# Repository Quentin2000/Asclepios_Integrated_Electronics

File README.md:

# Master Project

## Integration of a miniaturized O2 sensor into a space suit helmet.

#### Author: Quentin Delfosse
#### Academic Supervisor: Pr. Guillermo Villanueva
#### Technical Supervisor: Arnault Monoyer

## Repository files

This repository includes the following design files:
- **HW**: Kicad hardware files for the interface board and air quality sensor board.
- **SW**: Arduino files used to flash the ESP32 S2 Mini 1 computer.
- **SD**: Setup files for the SD card.

To access CAD design files, please refer to the Google Drive: https://drive.google.com/drive/folders/1vZVMf6BT2zpStATiHxgfttCtssU6DIhK?usp=drive_link.

## Introduction

Asclepios is a student-led project from Switzerland aiming at organizing simulations of manned space missions. For this purpose, the association rents existing infrastructure and builds its base inside. Therefore, by design, the mission will take place on Earth, where many parameters are different than on other celestial bodies. However, the analog astronauts will live together in close contact during the two weeks of the mission to experience the constraints of extraterrestrial environments during the Earth-based simulation. The project aims at optimizing their environment to make their mission as realistic as possible.

<br />

This project aims at integrating a miniaturized O2 sensor into a space suit helmet to monitor the user's breathable atmosphere. Both mechanical and electrical sensor integration will be required. Additionally, the sensor data will need to be processed. Thus, a graphical interface for the visualization of the O2 data in real time will need to be created.

<p align="center">
</img>
</p>

## Setup

### Hardware

The system is made of 3 stacked layers:
- **Upper stage**: Sensor stage (O2 + Air quality sensors)
- **Middle stage**: Interface stage 
- **Lower stage**: Main computer stage (ESP32 S2 Mini 1)

**CAREFUL: Before connecting two boards together, please make sure that the signals on both end match! This can be checked on the surface of the boards! Otherwise you may fry the sensors and the computer!**

To assemble the system, simply stack the layers on top of each other:
- Connect the main computer board (black one) to the interface board (long green one).
- **Make sure to check that the signals match: 3V3, Ground, 5V!**
- Insert the SD card into the interface board (bottom face).
- Connect the screen to the interface board (long white connector).
- Connect the Air quality sensor board (small green one) on top of the rooting board (long green one).
- **Again, check that the signals match: 3V3, Ground, 5V!**
- Place the stacked-up module on the 4 rails of the bottom cover. Only one orientation should fit.
- Connect the O2 sensor cable to the O2 sensor board.
- Insert the O2 sensor into the top cover hole, following the 2 rails and making sure that its cable comes out through the dedicated hole on the side.
- Place a foam on top of the interface board where the O2 sensor will be positioned (next to the air quality sensor).
- Close both end on the case together.
- Plug a USB cable to the micro usb port of the main computer and connect it to the portable battery.
- Power up the battery.

The screen should initialize after a couple of seconds and show a similar screen as the following one:
<p align="center">
</img>
</p>

The following figure shows a guidethrough of the procedure.
<p align="center">
</img>
</p>

### Software

To display the sensors data, you will need the following package:
```ruby
pip install pandas 
```

To retrieve the data from the SD card, the following procedure must be applied:
- Plug it into your computer
- Open the SD card folder and check the mission log which you want to display
- Open a terminal window
- Go to the SD card directory, something like the following for MAC OS users.
```ruby
 cd /Volumes/NO\ NAME 
```
- Type the following command, where **x** is the number of the mission log to display. You may also need to change to **python** instead of **python3** depending on your computer
```ruby
python3 display.py mission_log_x 
```

This will create a png file with the sensor graphs over the mission duration and an excel file with these values.
<p align="center">
</img>
</p>

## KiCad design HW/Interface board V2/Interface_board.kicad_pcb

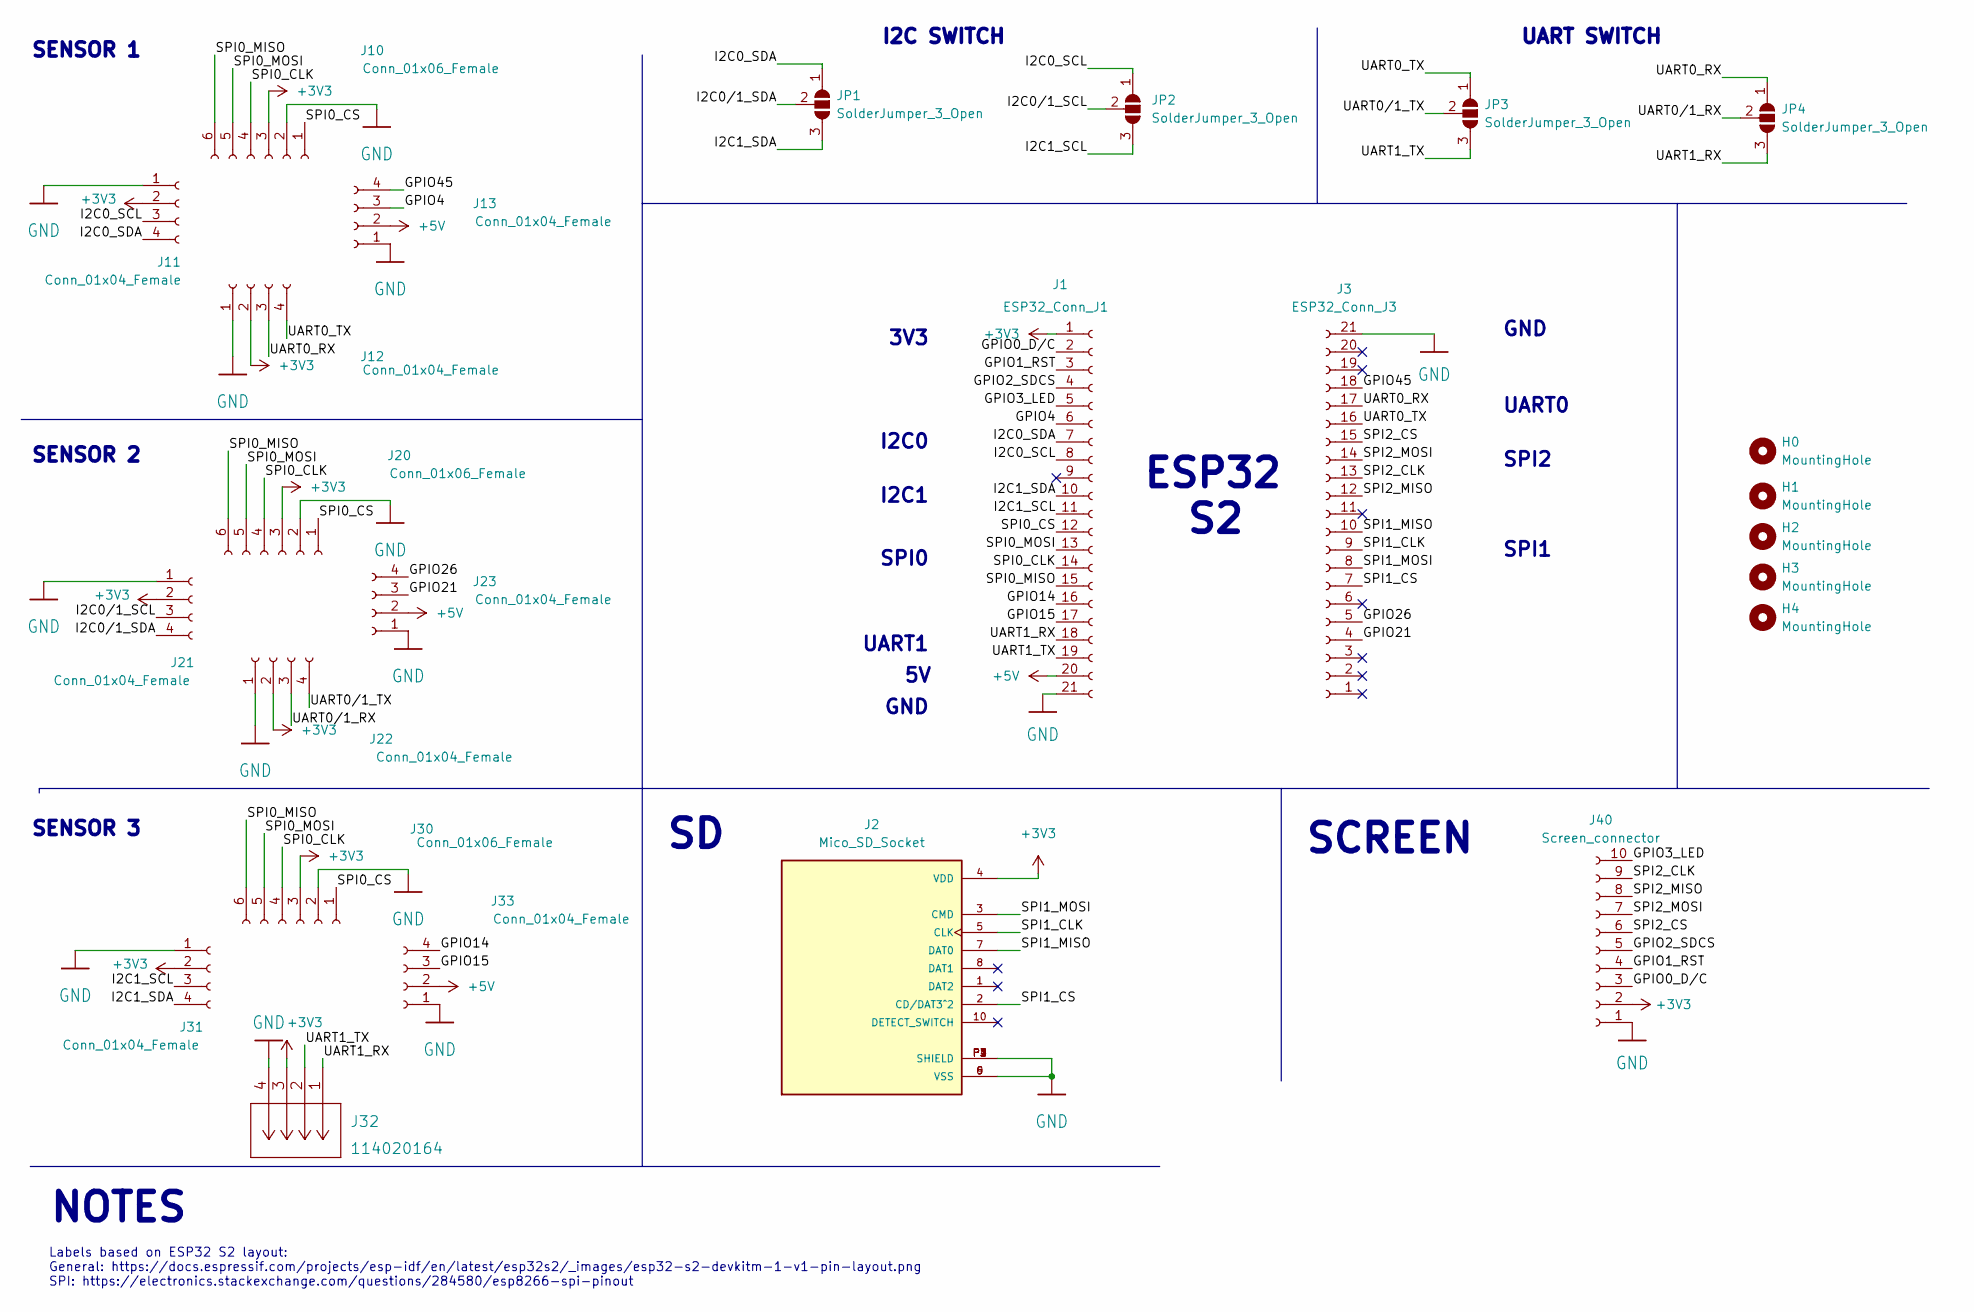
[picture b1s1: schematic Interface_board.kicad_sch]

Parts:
H0, H1, H2, H3, H4: MountingHole; MountingHole_2.2mm_M2_DIN965_Pad_TopBottom
J1: ESP32_Conn_J1; PinHeader_1x21_P2.54mm_Vertical
J2: Mico_SD_Socket; MOLEX_503398-1892; PARTREV 0
J3: ESP32_Conn_J3; PinHeader_1x21_P2.54mm_Vertical
J10, J20, J30: Conn_01x06_Female; PinSocket_1x06_P2.54mm_Vertical
J11, J12, J13, J21, J22, J23, J31, J33: Conn_01x04_Female; PinSocket_1x04_P2.54mm_Vertical
J32: 114020164; Conn_seed_114020164
J40: Screen_connector; Molex_PicoBlade_53048-1010_1x10_P1.25mm_Horizontal
JP1, JP2, JP3, JP4: SolderJumper_3_Open; SolderJumper-3_P1.3mm_Open_RoundedPad1.0x1.5mm

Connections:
+3V3: J1.1, J2.4 (VDD), J10.3, J11.2, J12.2, J20.3, J21.2, J22.2, J30.3, J31.2, J32.3, J40.2
+5V: J1.20, J13.2, J23.2, J33.2
/GPIO0_D/C: J1.2, J40.3
/GPIO1_RST: J1.3, J40.4
/GPIO2_SDCS: J1.4, J40.5
/GPIO3_LED: J1.5, J40.10
/GPIO4: J1.6, J13.3
/GPIO14: J1.16, J33.4
/GPIO15: J1.17, J33.3
/GPIO21: J3.4, J23.3
/GPIO26: J3.5, J23.4
/GPIO45: J3.18, J13.4
/I2C0_SCL: J1.8, J11.3, JP2.1 (A)
/I2C0_SDA: J1.7, J11.4, JP1.1 (A)
/I2C0/1_SCL: J21.3, JP2.2 (C)
/I2C0/1_SDA: J21.4, JP1.2 (C)
/I2C1_SCL: J1.11, J31.3, JP2.3 (B)
/I2C1_SDA: J1.10, J31.4, JP1.3 (B)
/SPI0_CLK: J1.14, J10.4, J20.4, J30.4
/SPI0_CS: J1.12, J10.1, J20.1, J30.1
/SPI0_MISO: J1.15, J10.6, J20.6, J30.6
/SPI0_MOSI: J1.13, J10.5, J20.5, J30.5
/SPI1_CLK: J2.5 (CLK), J3.9
/SPI1_CS: J2.2 (CD/DAT3^2), J3.7
/SPI1_MISO: J2.7 (DAT0), J3.10
/SPI1_MOSI: J2.3 (CMD), J3.8
/SPI2_CLK: J3.13, J40.9
/SPI2_CS: J3.15, J40.6
/SPI2_MISO: J3.12, J40.8
/SPI2_MOSI: J3.14, J40.7
/UART0_RX: J3.17, J12.3, JP4.1 (A)
/UART0_TX: J3.16, J12.4, JP3.1 (A)
/UART0/1_RX: J22.3, JP4.2 (C)
/UART0/1_TX: J22.4, JP3.2 (C)
/UART1_RX: J1.18, J32.1, JP4.3 (B)
/UART1_TX: J1.19, J32.2, JP3.3 (B)
GND: J1.21, J2.6 (VSS), J2.9 (VSS), J2.P1 (SHIELD), J2.P2 (SHIELD), J2.P3 (SHIELD), J2.P4 (SHIELD), J3.21, J10.2, J11.1, J12.1, J13.1, J20.2, J21.1, J22.1, J23.1, J30.2, J31.1, J32.4, J33.1, J40.1

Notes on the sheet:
SENSOR 3
SCREEN
GND
UART1
Labels based on ESP32 S2 layout: General: https://docs.espressif.com/projects/esp-idf/en/latest/esp32s2/_images/esp32-s2-devkitm-1-v1-pin-layout.png SPI: https://electronics.stackexchange.com/questions/284580/esp8266-spi-pinout
3V3
I2C SWITCH
I2C1
ESP32 S2
I2C0
SPI1
SPI0
SENSOR 1
NOTES
UART0
UART SWITCH
SPI2
SENSOR 2

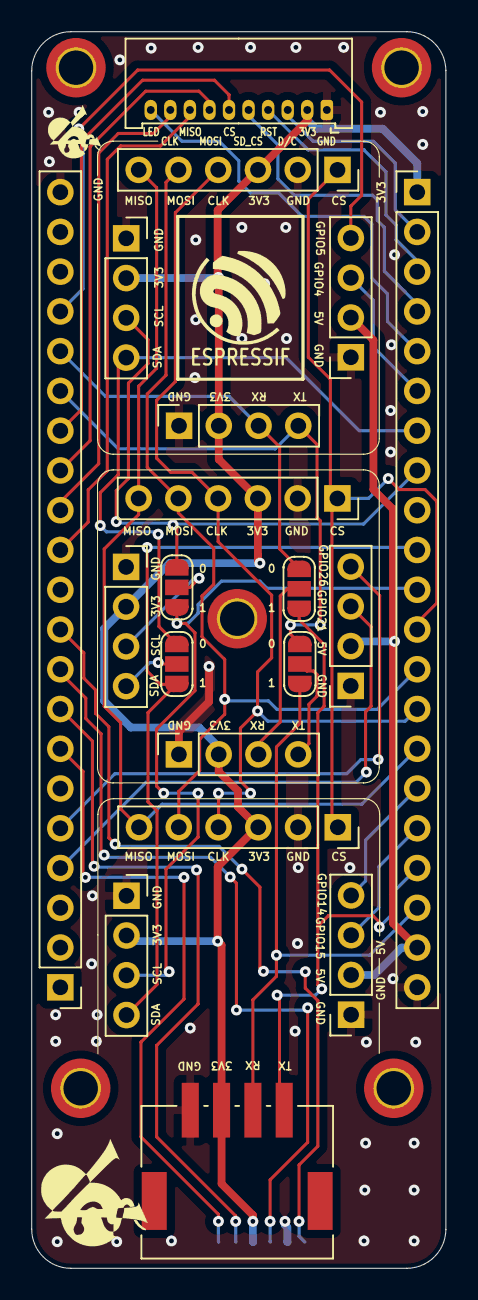
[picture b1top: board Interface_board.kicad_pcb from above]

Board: 2 copper layers, 26.5 x 79.0 mm, 25 parts (1 on the bottom side), 37 nets.

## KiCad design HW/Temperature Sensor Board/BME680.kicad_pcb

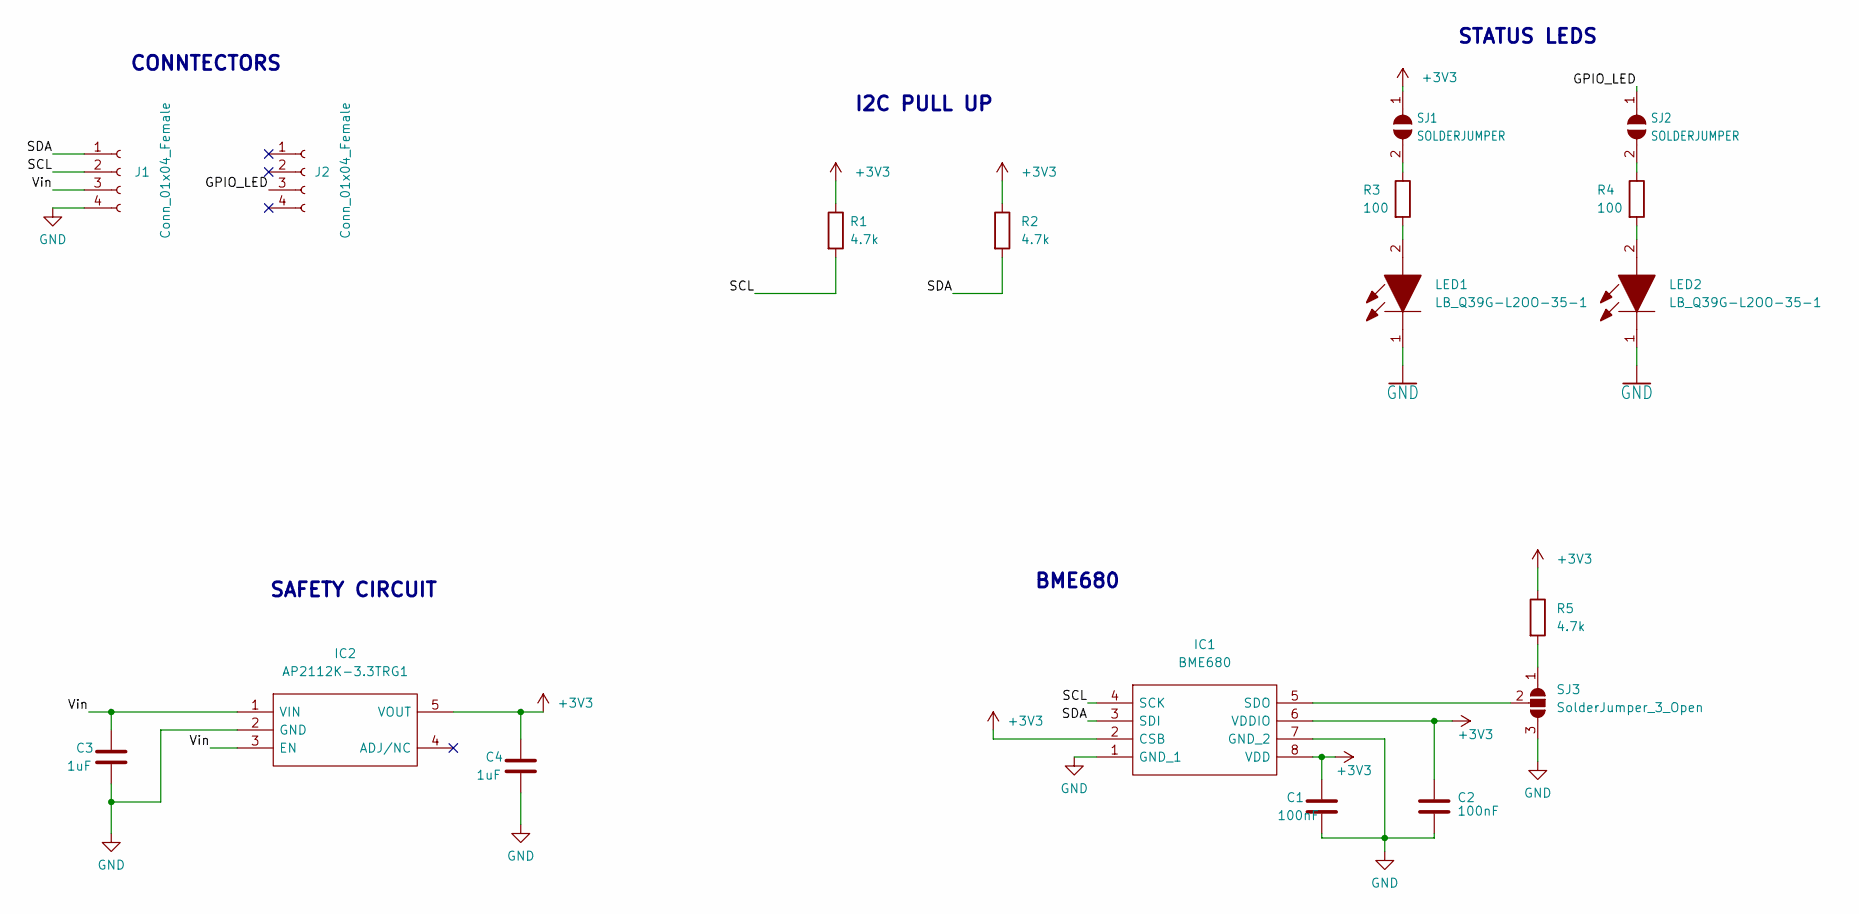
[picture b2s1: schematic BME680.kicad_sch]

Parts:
C1, C2: 100nF; C_0603_1608Metric
C3, C4: 1uF; C_0603_1608Metric
IC1: BME680; Mouser Part Number 262-BME680
IC2: AP2112K-3.3TRG1; SOT95P282X130-5N; Mouser Part Number 621-AP2112K-3.3TRG1
J1, J2: Conn_01x04_Female; PinHeader_1x04_P2.54mm_Vertical
LED1, LED2: LB_Q39G-L2OO-35-1; LEDC1608X40N; Mouser Part Number 720-LBQ39GL2N2351
R1, R2, R5: 4.7k; R_0603_1608Metric
R3, R4: 100; R_0603_1608Metric
SJ1, SJ2: SOLDERJUMPER; SolderJumper-2_P1.3mm_Open_RoundedPad1.0x1.5mm
SJ3: SolderJumper_3_Open; SolderJumper-3_P1.3mm_Open_RoundedPad1.0x1.5mm

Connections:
+3V3: C1.1, C2.1, C4.1, IC1.2 (CSB), IC1.6 (VDDIO), IC1.8 (VDD), IC2.5 (VOUT), R1.1, R2.1, R5.1, SJ1.1
/GPIO_LED: J2.3, SJ2.1
/SCL: IC1.4 (SCK), J1.2, R1.2
/SDA: IC1.3 (SDI), J1.1, R2.2
/Vin: C3.1, IC2.1 (VIN), IC2.3 (EN), J1.3
GND: C1.2, C2.2, C3.2, C4.2, IC1.1 (GND_1), IC1.7 (GND_2), IC2.2 (GND), J1.4, LED1.1, LED2.1, SJ3.3 (B)
unnamed: IC1.5 (SDO), SJ3.2 (C)
unnamed: LED1.2, R3.2
unnamed: LED2.2, R4.2
unnamed: R3.1, SJ1.2
unnamed: R4.1, SJ2.2
unnamed: R5.2, SJ3.1 (A)

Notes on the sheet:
BME680
STATUS LEDS
I2C PULL UP
CONNTECTORS
SAFETY CIRCUIT

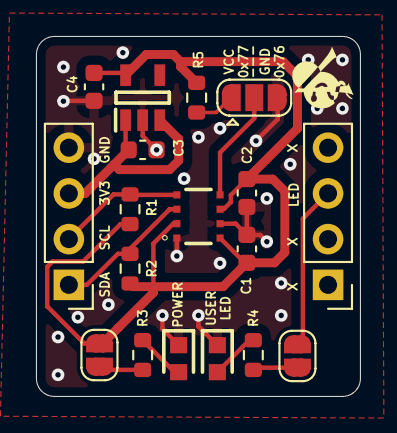
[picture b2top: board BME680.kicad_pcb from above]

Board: 2 copper layers, 18.0 x 20.0 mm, 18 parts (0 on the bottom side), 12 nets.

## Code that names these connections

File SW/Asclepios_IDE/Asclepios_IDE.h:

#include <Wire.h>
#include <SPI.h>
#include <TFT_eSPI.h>
#include <WiFi.h>
#include <HardwareSerial.h>
#include <Adafruit_Sensor.h>
#include "Adafruit_BME680.h"
#include "FS.h"
#include "SD.h"
#include "SPI.h"

//#include <stdlib.h>

#define __min(a,b) ((a)<(b)?(a):(b)) 
#define __max(a,b) ((a)>(b)?(a):(b))

// WIFI Setup
extern char ssid [64];
extern char password [64];
extern String HOST_NAME; // Local Host's IP address to be changed 
// String PATH_NAME   = "/insert_temp.php";
// String queryString = "?temperature=30.5";

// UART1 (O2 sensor)
#define RX1 16
#define TX1 17
extern HardwareSerial Uart1;
extern float O2_val; // [%] default value
extern float old_o2;    // [%]
extern float min_O2; // [%] according to safety regulations
extern float max_O2; // [%] according to safety regulations

// I2C1 (BME sensor)
#define BME_SDA 5
#define BME_SCL 6
#define BME_ADDR 0x76
#define SEALEVELPRESSURE_HPA (1013.25)
extern Adafruit_BME680 bme; // I2C
#define ATM 1013.25 // 1 atm = 1013,25 hPa
extern float min_pres; // [*C] according to safety regulations
extern float max_pres; // [*C] according to safety regulations
extern float old_pres;
extern float min_temp; // [*C] according to safety regulations
extern float max_temp; // [*C] according to safety regulations
extern float old_temp;
extern float min_hum; // [%] according to safety regulations
extern float max_hum; // [%] according to safety regulations
extern float old_hum;
extern float max_alt; // [m] for display purposes
extern float min_alt; // [m] for display purposes
extern float old_alt;
extern float max_gas; // [KOhm] for display purposes
extern float min_gas; // [KOhm] for display purposes
extern float old_gas;

// /!\ CAREFUL, DO NOT CHOOSE MAX_VAL = 2*MIN_VAL AS A DIVISION BY 0 ERROR WILL OCCUR SOMEHOW /!\

// SPI1 (SD card)
#define SPI1_MISO   MISO  // 37
#define SPI1_MOSI   MOSI  // 35
#define SPI1_SCLK   SCK   // 36
#define SPI1_SS     SS    // 34
extern SPIClass * SPI1;
extern uint8_t cardType;
extern uint16_t mission_log_nbr;
extern char mission_log_file [64];

// SPI2 (Screen) (defined in the Arduino/libraries/TFT_eSPI/User_Setup.h file)
//#define SPI2_MISO   39
//#define SPI2_MOSI   41
//#define SPI2_SCLK   40
//#define SPI2_SS     42
extern TFT_eSPI tft;       // Invoke custom library
extern float Text_font;
extern uint16_t x_o2;
extern uint16_t y_o2;
extern uint16_t x_hum;
extern uint16_t y_hum;
extern uint16_t x_temp;
extern uint16_t y_temp;
extern uint16_t x_pres;
extern uint16_t y_pres;
extern uint16_t x_gas;
extern uint16_t y_gas;
extern uint16_t x_alt;
extern uint16_t y_alt;
#define DEG2RAD 0.0174532925
extern byte base_green; // over 256 values
extern int brightness; // [%]
extern int graph_thickness;
extern float screen_refresh_thresh;
extern int init_loop;

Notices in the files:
parts and their libraries:
Copyright 2021 Accelerated Designs. All rights reserved.
